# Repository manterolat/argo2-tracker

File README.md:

# Argo 2 Tracker

High Altitude Balloon tracker designed for the Argo 2 launch by the Near Space Program at the International School of Panama.

Tracker transmits temperature, pressure and humidity data, as well as location coordinates and other status information.

The GroundStation program shows any data received, along with signal strength and CRC checking. It can also upload new data to the online tracker at [HabHub](https://tracker.habhub.com).

Included are the PCB schematics (made in Eagle CAD) and software of the tracker and receiver, as well as the Ground Station program which runs on the tracking computer.

The software for the tracker and receiver is written in Arduino / C++, while the Ground Station written in Python.

## Table of Contents
 * [Parts and Components](#parts)
 * [Installation](#installation)
 * [Usage](#usage)
 * [Testing](#testing)
 * [Printed Circuit Boards](#pcbs)
 * [Launches](#launch)

## Parts and Components
### Tracker:
 * [Adafruit Feather M0](https://www.adafruit.com/product/269), or [Teensy 3.x](https://www.pjrc.com/store/teensy32.html) with [Feather adapter](https://www.adafruit.com/products/3200)
 * U-Blox NEO 6/7/8 Serial GPS module such as [this](https://www.amazon.com/Antenna-AeroQuad-Multirotor-Quadcopter-Aircraft/dp/B00RCP9MLY/)
 * ~~[MAX31855 thermocouple amplifier](https://www.adafruit.com/products/269) (and [thermocouple](https://www.adafruit.com/products/270))~~ Doesn't work
 * [BME280 module](https://www.adafruit.com/products/2652): Pressure, humidity and temperature sensor
 * RFM95W Transceiver

### Receiver:
 * [Adafruit Feather M0](https://www.adafruit.com/product/269)
 * RFM95W Transceiver
 * PCB SMA connector (if using SMA cable for antenna)

## Installation
To download the files in this repository run:

`git clone https://github.com/manterolat/argo2-tracker.git`

### Tracker:
#### Software
 * [Arduino IDE](https://www.arduino.cc/en/Main/Software) (1.6.0 and above should work)
 * If using *Teensy 3.x*: Install [Teensyduino](http://www.pjrc.com/teensy/teensyduino.html) (tested with Teensyduino 1.29)
 * If using *Feather M0*: follow [these](https://learn.adafruit.com/adafruit-feather-m0-basic-proto/setup) instructions

#### Arduino Libraries
 * [Adafruit Unified Sensor Driver](https://github.com/adafruit/Adafruit_Sensor)
 * [Adafruit BME280](https://github.com/adafruit/Adafruit_BME280_Library)
 * ~~Only with *Teensy* setup: [Adafruit MAX31855](https://github.com/adafruit/Adafruit-MAX31855-library) (version 1.0.3 or higher for SPI Transactions)~~ Doesn't work
 * If using *Teensy 3.x*: [RadioHead](https://github.com/PaulStoffregen/RadioHead) (Paul Stoffregen's version for Teensy)
 * If using *Feather M0*: [RadioHead](http://www.airspayce.com/mikem/arduino/RadioHead/) (Regular, updated version) 
 * ~~[TinyGPS++](https://github.com/mikalhart/TinyGPSPlus)~~ Broken for non-AVR chips: use [this](https://github.com/manterolat/argo2-tracker/files/601752/TinyGPSPlus.zip) modified version instead

### Receiver:
#### Software
 * [Arduino IDE](https://www.arduino.cc/en/Main/Software) (1.6.0 and above should work)

#### Arduino Libraries
 * [RadioHead](https://github.com/PaulStoffregen/RadioHead)

### Ground Station:
GroundStation runs on Python 2.7, and requires the following modules:
 * *crcmod* for CRC checking
 * *pyqrcode* for generating QR codes
 * *pyserial* for serial communication

To install these (using *pip*) run:

`pip install crcmod pyqrcode pyserial`

## Usage
After setting up the software and libary requirements you should be able to upload the tracker and receiver programs, as well as run the Ground Station.

### Tracker:
Open `/src/Argo2_Tracker/Argo2_Tracker.ino` in the Arduino IDE.

Before compiling and uploading to the Feather/Teensy make sure to configure the tracker by changing the following lines in the program: 
```C++
// Tracker callsign: change to your tracker's callsign
#define CALLSIGN "CHANGE_ME"

// Debug messages: uncomment the following line to enable printing to serial (for testing purposes)
//#define DEBUG

...

// Select either Teensy 3.x or Feather M0
#define TEENSY
//#define FEATHER
```

Leaving `#define DEBUG` uncommented will compile the Serial messages, which takes up space and cycles in the microcontroller.

Finally, select the board type and serial port in the Arduino IDE and upload.  

### Receiver:
Open `Argo2_Receiver.ino` with the Arduino IDE, then select the Feather M0 from the boards list and upload.

### Ground Station:
If running on macOS with Python 2 installed manually, double-clicking `GroundStation.py` should start the program.

Otherwise, open a terminal in the argo2-tracker directory and run:

```bash
cd GroundStation
python GroundStation.py
```

The program will keep a log in the form of files: `GroundStation.log` and `sentences.log`.

**Caution: Don't toggle the _Online_ checkbox until you have setup your tracker on [HabHub](https://tracker.habhub.com) and are ready to launch/test.**

## Testing
Things to keep in mind before launch:
 * *Cut the thermocouple cable as short as possible* while keeping a small piece outside. We found that this reduced interference and/or resistance in the cable and improved the accuracy of measurements.
 * For the BME280 (pressure and humidity sensor) it's best to use cables and *place the module on the outside of the capsule*.
 * If placing the BME280 outside, *cover the sensor with a small piece of cotton/fabric using tape* in order to block wind which could affect measurements.

Only the *Adafruit Feather M0* configuration (without thermocouple sensor) has being tested so far. Since then there have been a few changes to the tracker and receiver programs (mostly changing Serial.println to Snprintln).

The tracker also can't use the BME280 through SPI at the same time as the RFM95W radio due to SPI Transaction issues with the RadioHead library.
For this reason, **to use the BME280 you will need to connect the SCL and SDA pins of the BME280 to those of the Feather externally to use I2C instead** (soldering wires externally).

## Printed Circuit Boards
Both of these boards can be used with headers (for removable/replaceable components), or with the components soldered directly unto the board. I recommend the first method.

If using headers note that the RFM95W module needs *2.0mm* headers, instead of regular 2.54mm headers.

The PCBs used in the Argo 2 launch were printed by [OSH Park](https://oshpark.com/) and functioned perfectly.

### Tracker:
Note that there is an issue with the buzzer MOSFET and its connections at the moment. If you plan to use this board with a buzzer, you will have to either fix the MOSFET connections or connect the components separately.

### Receiver:
This board supports the use of a PCB to SMA adapter if needed.

## Launches
### **April 23, 2016**: (Argo-2) 
We launched the Argo 2 capsule on April 23, 2016 using the Feather M0 setup without the thermocouple (due to SPI issues). We received data throughout most of flight, which reached `33 km` altitude, and used HabHub to follow the capsule.
Unfortunately, the capsule landed in a mountainous area that made recovery impossible.

The data revealed an average vertical speed of `2.3 m/s` (very low) and an estimated flight time of 295 minutes.

### **November 28, 2016**: (CP-1)

We launched the CP-1 capsule on November 28, 2016, and succesfully recovered it! GoPro camera took many photos throughout the mission.

The capsule rose to around `33 km` at an average vertical speed of `4.5 m/s`. The mission lasted 149 minutes.

### **June 4, 2017**: (CP-2)
Another successfull recovery with the same setup!

The capsule rose to around `27 km` at an average vertical speed of `5.5 m/s`. The mission lasted 136 minutes.

In the future, the NSP team will be using the [Pi in the Sky](http://www.pi-in-the-sky.com/) board due to its widespread support and easy configurability. I wish them the best of luck in future launches!

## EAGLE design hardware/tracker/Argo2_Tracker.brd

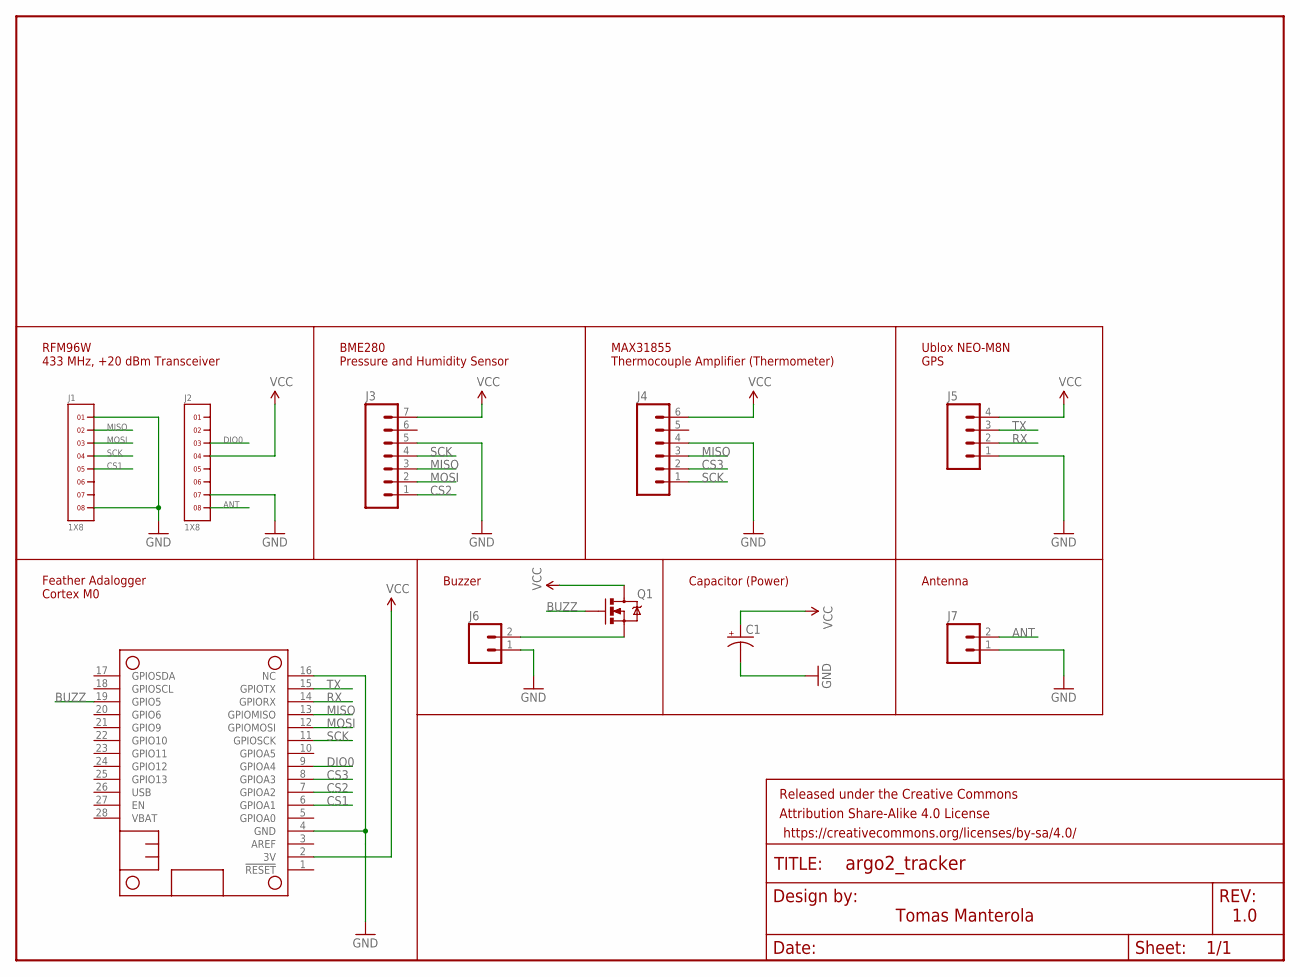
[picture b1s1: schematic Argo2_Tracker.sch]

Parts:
C1: CAP_POLPTH4; CPOL-RADIAL-1000UF-25V
FRAME1: FRAME-LETTERNO_PACKAGE; DUMMY
J1, J2: 1X8
J3: M07; 1X07
J4: M06SILK_FEMALE_PTH; 1X06
J5: M041X04_NO_SILK; 1X04_NO_SILK
J6, J7: M02PTH; 1X02
MS1: FEATHERWING_NODIM; FEATHERWING_DIM
Q1: MOSFET-NCHANNELFQP30N06L; TO220V

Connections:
ANT: J2.8, J7.2
BUZZ: MS1.19 (GPIO5), Q1.1 (G)
CS1: J1.5, MS1.6 (GPIOA1)
CS2: J3.1, MS1.7 (GPIOA2)
CS3: J4.2, MS1.8 (GPIOA3)
DIO0: J2.3, MS1.9 (GPIOA4)
GND: C1.2 (-), J1.1, J1.8, J2.7, J3.5, J4.4, J5.1, J6.1, J7.1, MS1.4 (GND), MS1.16 (NC)
MISO: J1.2, J3.3, J4.3, MS1.13 (GPIOMISO)
MOSI: J1.3, J3.2, MS1.12 (GPIOMOSI)
unnamed: J6.2, Q1.3 (S)
RX: J5.2, MS1.14 (GPIORX)
SCK: J1.4, J3.4, J4.1, MS1.11 (GPIOSCK)
TX: J5.3, MS1.15 (GPIOTX)
VCC: C1.1 (+), J2.4, J3.7, J4.6, J5.4, MS1.2 (3V), Q1.2 (D)

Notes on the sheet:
RFM96W 433 MHz, +20 dBm Transceiver
Tomas Manterola
1.0
Feather Adalogger Cortex M0
BME280 Pressure and Humidity Sensor
MAX31855 Thermocouple Amplifier (Thermometer)
Ublox NEO-M8N GPS
Buzzer
Antenna
Capacitor (Power)

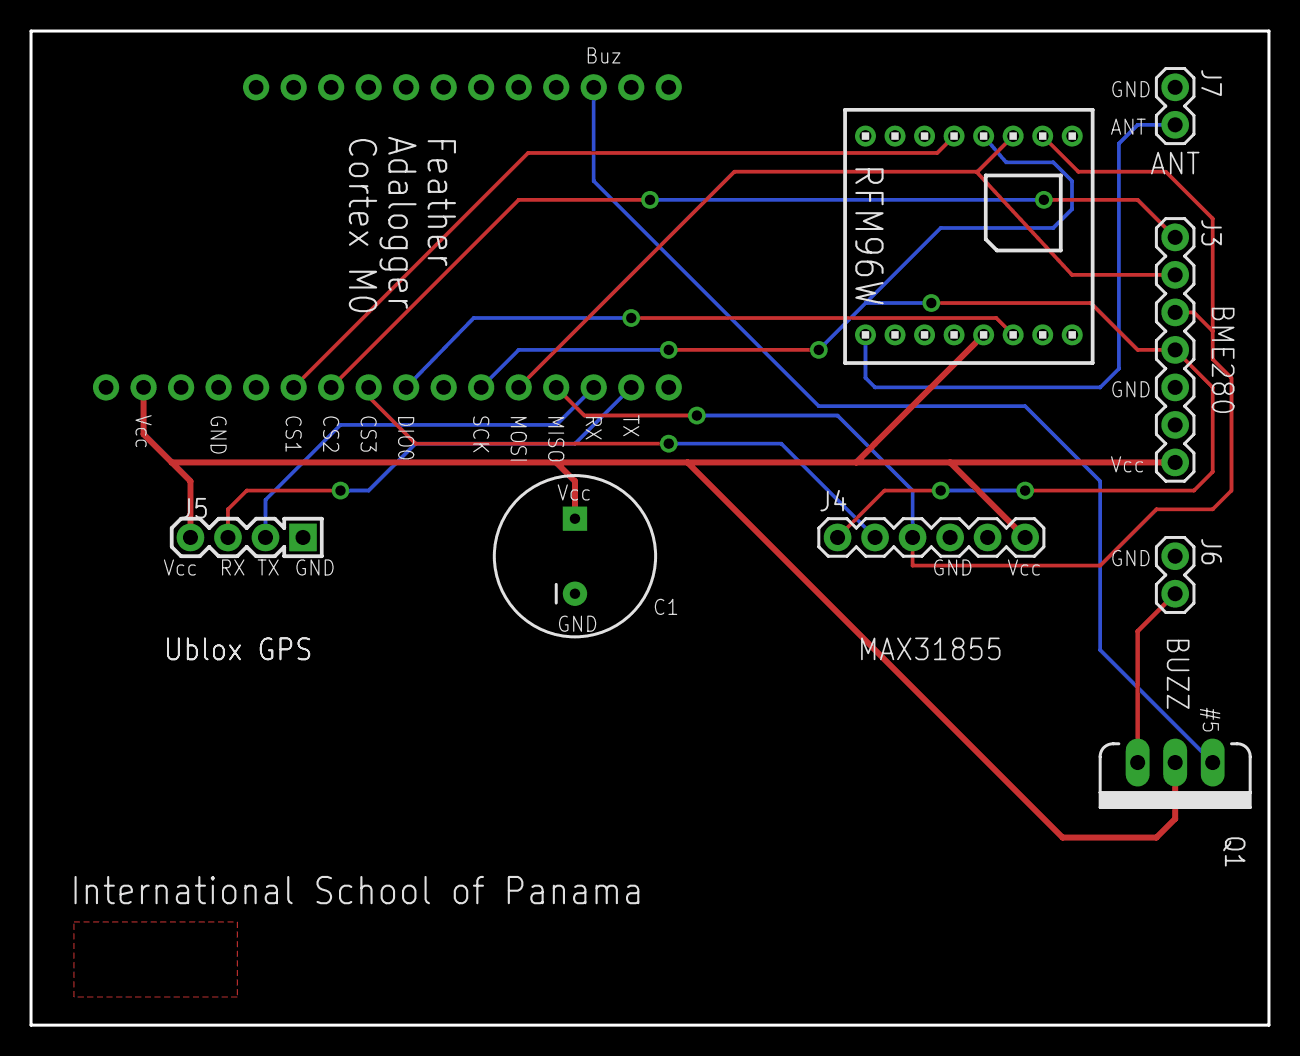
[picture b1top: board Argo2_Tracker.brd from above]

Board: 2 copper layers, 83.8 x 67.3 mm, 11 parts (0 on the bottom side), 14 nets.

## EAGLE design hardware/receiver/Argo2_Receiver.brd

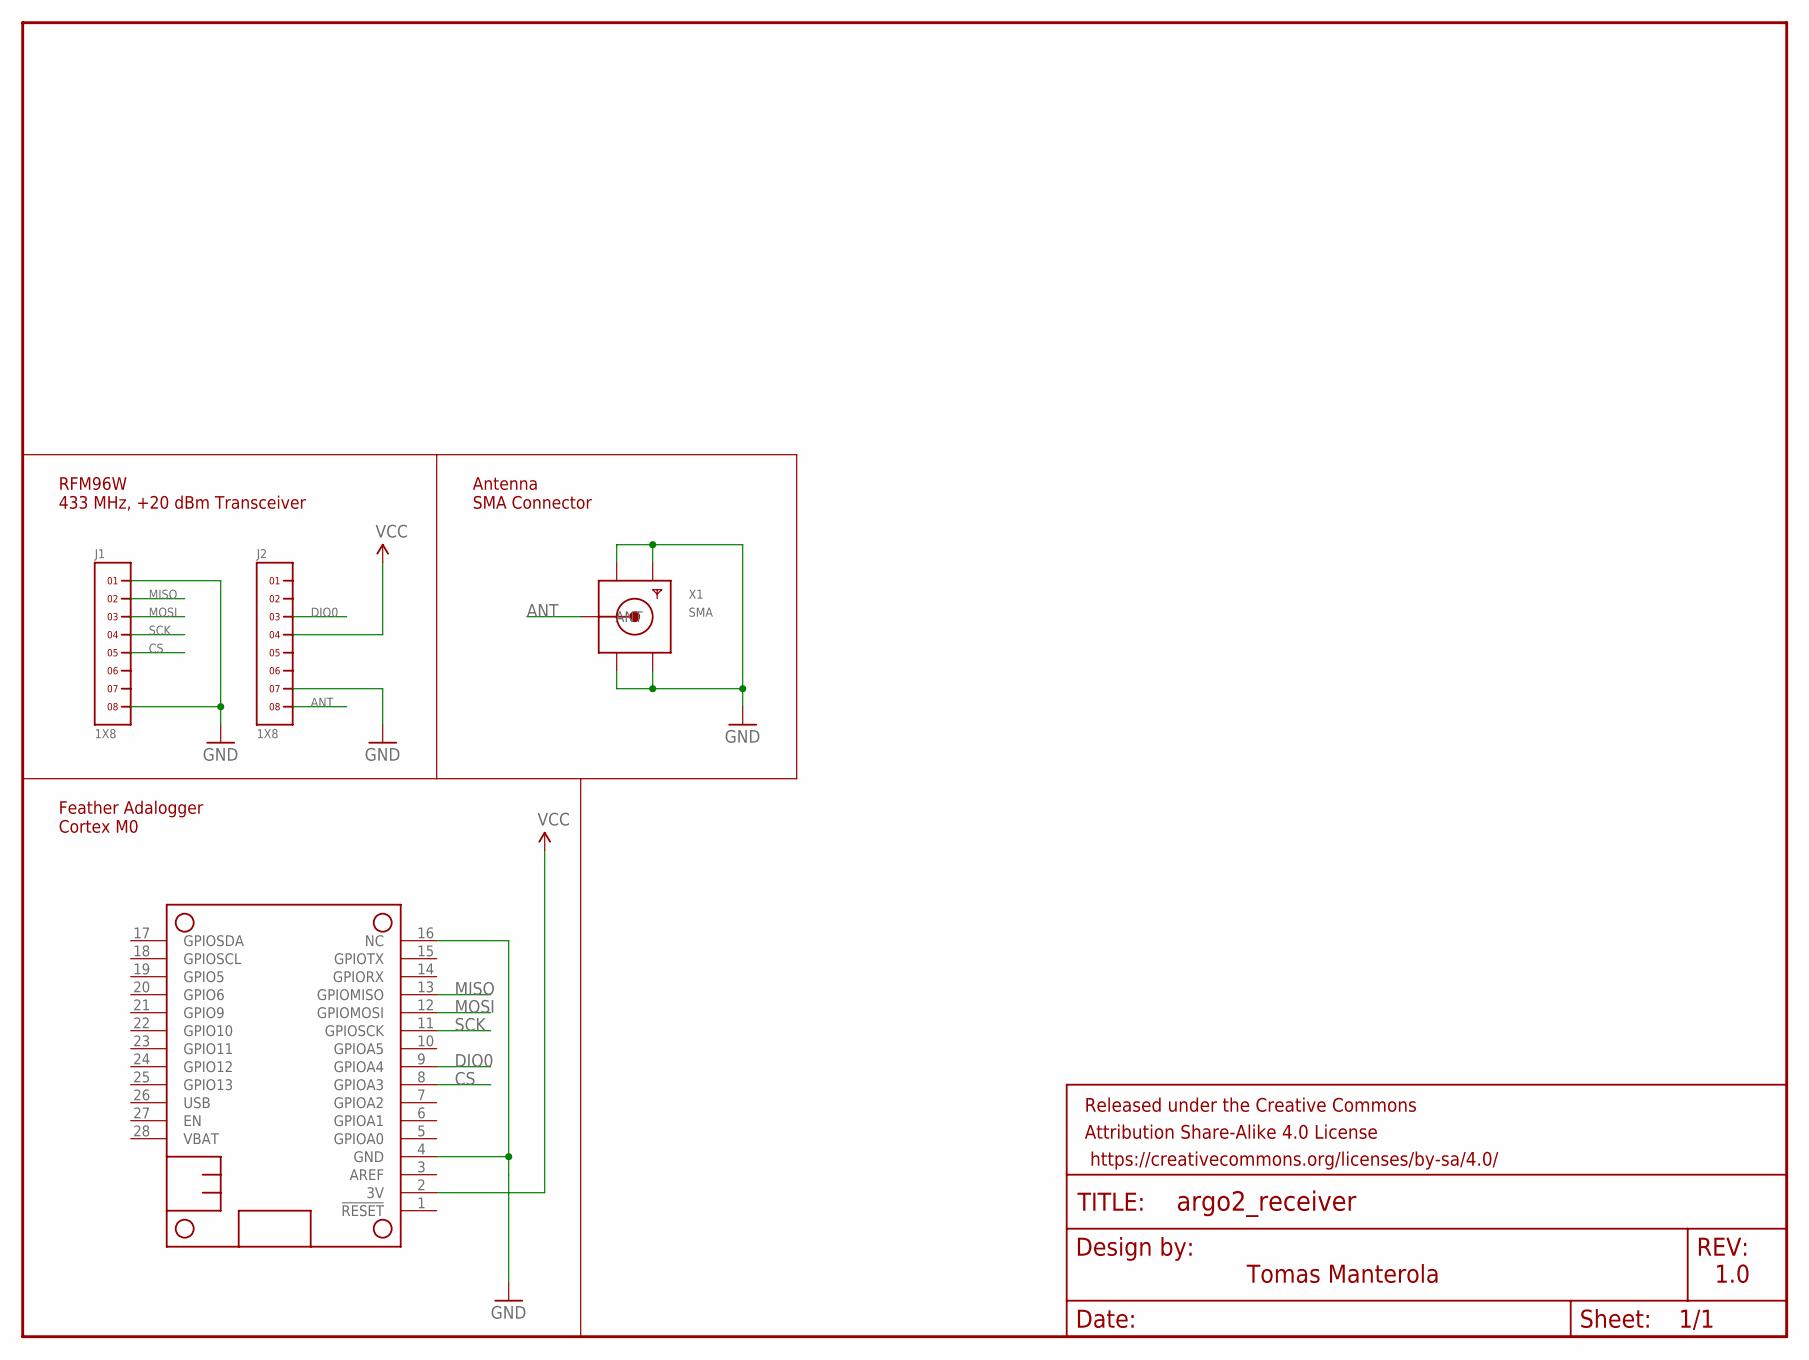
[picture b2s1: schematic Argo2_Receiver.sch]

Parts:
FRAME1: FRAME-LETTERNO_PACKAGE; DUMMY
J1, J2: 1X8
MS1: FEATHERWING_NODIM; FEATHERWING_DIM
X1: SMA; SMA_EDGELAUNCH

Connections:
ANT: J2.8, X1.P (ANT)
CS: J1.5, MS1.8 (GPIOA3)
DIO0: J2.3, MS1.9 (GPIOA4)
GND: J1.1, J1.8, J2.7, MS1.4 (GND), MS1.16 (NC), X1.GND@1 (GND4), X1.GND@2 (GND3), X1.GND@3 (GND2), X1.GND@4 (GND1)
MISO: J1.2, MS1.13 (GPIOMISO)
MOSI: J1.3, MS1.12 (GPIOMOSI)
SCK: J1.4, MS1.11 (GPIOSCK)
VCC: J2.4, MS1.2 (3V)

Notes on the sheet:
RFM96W 433 MHz, +20 dBm Transceiver
Tomas Manterola
1.0
Feather Adalogger Cortex M0
Antenna SMA Connector

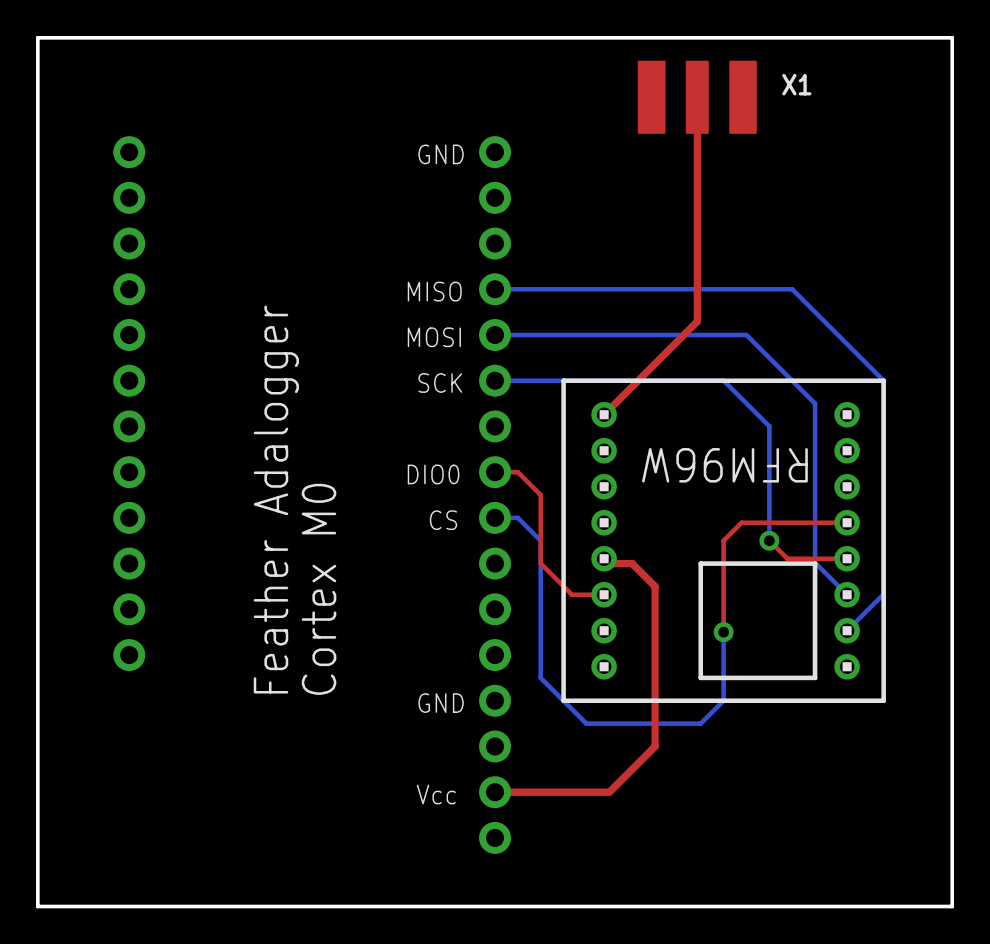
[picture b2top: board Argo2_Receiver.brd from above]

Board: 2 copper layers, 50.8 x 48.3 mm, 5 parts (0 on the bottom side), 8 nets.

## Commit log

2016-11-10 Add QR code functionality to Ground Station
    A QR code that users can scan to open a mapping app on their mobile
    device is now displayed on the main screen of the Ground Station
    program.
    The last location received from the tracker is encoded in the
    QR code and displayed on the map. The QR code is updated whenever a new
    valid message is received.
2016-11-10 Change serial port write_timeout to 5 seconds in Ground Station
    This is a minor change to how the program writes to the serial port.
    Before, the serial port would block indefinitely if a write was
    unsuccessful (write_timeout=None). Now the serial port will display an
    error and the program will continue if no data can be sent after 5
    seconds (write_timeout=5).
2016-11-10 Bump Ground Station to version 1.1.0
2016-11-10 Add Ground Station README.md
2016-11-11 Merge Feather and Teensy trackers and small changes Merged both Argo2_Tracker_Feather and Argo2_Tracker_Teensy into Argo2_Tracker, keeping original functionality.
    Code was also improved/cleaned-up. The program now uses spaces instead of tabs, unused commented code was removed, and some comments/messages were improved.
    Main changes:
    - Merged Feather and Teensy trackers into one
    - Cleaned up code (all tabs now spaces, removed unused code)
    - Improved state transition values for RISING and FALLING
    - Debug messages now disabled by default
2016-11-11 Cleanup receiver code
    Small cleanup update. Changed tabs to spaces and improved formatting
    slightly.
2016-11-19 Fix #2 and change default settings
    Fix pin assignment issue with Teensy to Feather adapter, as well as
    changing various defaults in the tracker.
    Changes:
    - Pins when using Teensy changed
    - Feather is now default board (previously Teensy)
    - MAX31855 now disabled (SPI issues)

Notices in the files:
parts and their libraries:
SparkFun-Aesthetics: Licensing: Creative Commons ShareAlike 4.0 International - https://creativecommons.org/licenses/by-sa/4.0
SparkFun-Aesthetics: Released under the Creative Commons Attribution Share-Alike 4.0 License
SparkFun-Aesthetics: https://creativecommons.org/licenses/by-sa/4.0
